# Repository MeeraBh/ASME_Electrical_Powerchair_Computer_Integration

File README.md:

# ASME Electrical Powerchair Computer Integration
This is repo contains the schematic, pcb, and gerber files from Kicad for a custom ortholinear split keyboard PCB as well as all files needed to order the pcb on JLCPCB.

This project was made for ASME - Product Development and will be shown at Engineering Open House.  

It is intended to be used for a powerchair in which the PCB contains the peripherals for the computer minus the monitor itself in which the mainboard of the computer is connected to the powerchair.  These peripherals are the keyboard itself, 2 OLED screens (Nice!Views), and 2 joysticks.  There are also a total of 3 microcontrollers (Nice!Nanos) that can connect to each other through bluetooth and communicate.  The keyboard can also be used as split design or merged together as a full keyboard due to the connections in the center.

# Keyboard
PCB

3D View Front

3D View Back

Schematic

Gerber, BOM, and CTL (.pos) files in repo that are compatible with JLCPCB printing.

Details on full project: https://erinpc.vercel.app

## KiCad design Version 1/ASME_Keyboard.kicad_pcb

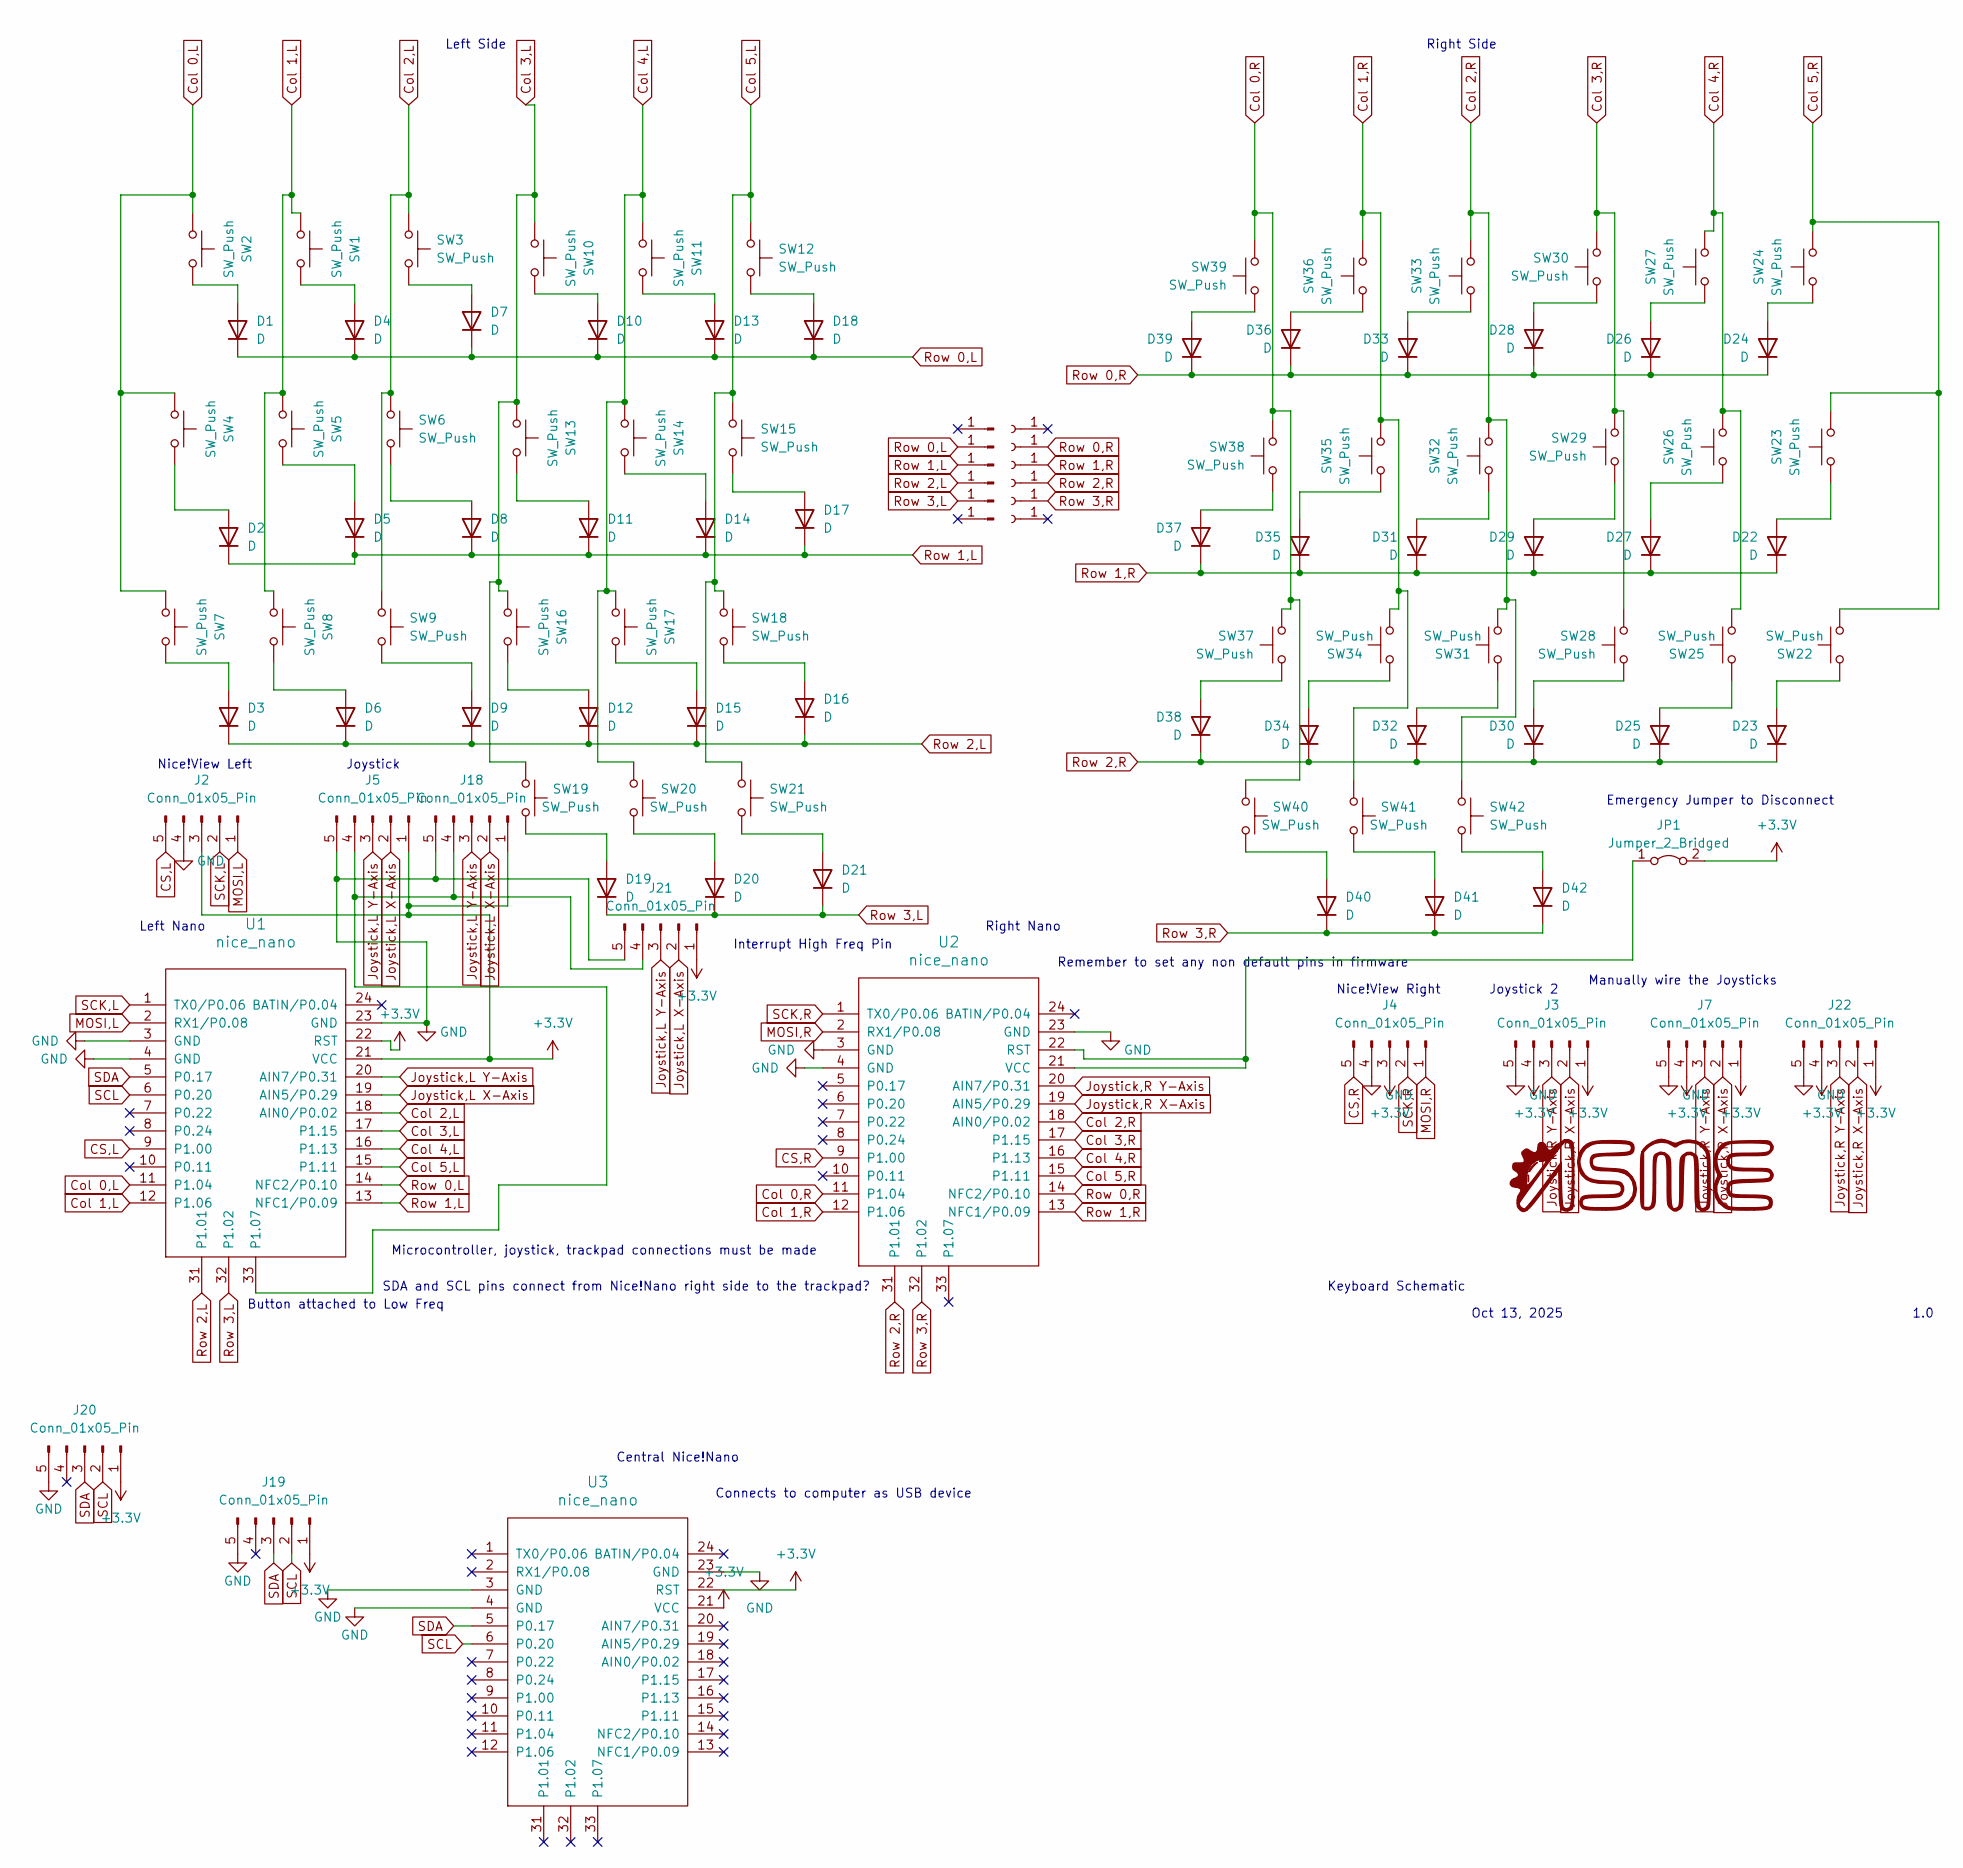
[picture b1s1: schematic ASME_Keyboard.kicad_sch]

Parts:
D1, D2, D3, D4, D5, D6, D7, D8, D9, D10, D11, D12, D13, D14, D15, D16, D17, D18, D19, D20, D21, D22, D23, D24, D25, D26, D27, D28, D29, D30, D31, D32, D33, D34, D35, D36, D37, D38, D39, D40, D41, D42: D; D_1206_3216Metric
J1, J8, J9, J10, J11, J12: Conn_01x01_Pin; MF_Connectors-POGO_PIN_70-9150
J2, J4: Conn_01x05_Pin; nice_view
J3, J5: Conn_01x05_Pin; Joycon_edited_5pin
J6, J13, J14, J15, J16, J17: Conn_01x01_Socket; MF_Connectors-POGO_PIN_70-9150
J7, J18, J19, J20, J21, J22: Conn_01x05_Pin; PinHeader_1x05_P2.54mm_Vertical
JP1: Jumper_2_Bridged; SolderJumper-2_P1.3mm_Open_Pad1.0x1.5mm
SW1, SW2, SW3, SW4, SW5, SW6, SW7, SW8, SW9, SW10, SW11, SW12, SW13, SW14, SW15, SW16, SW17, SW18, SW19, SW20, SW21, SW22, SW23, SW24, SW25, SW26, SW27, SW28, SW29, SW30, SW31, SW32, SW33, SW34, SW35, SW36, SW37, SW38, SW39, SW40, SW41, SW42: SW_Push; Kailh_socket_MX
U1, U2, U3: nice_nano

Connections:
+3.3V: J2.3, J3.1, J3.4, J4.3, J5.1, J7.1, J7.4, J18.1, J19.1, J20.1, J21.1, J22.1, J22.4, JP1.2 (B), U1.21 (VCC), U1.22 (RST), U3.21 (VCC), U3.22 (RST)
CS,L: J2.5, U1.9 (P1.00)
CS,R: J4.5, U2.9 (P1.00)
Col 0,L: SW2.1, SW4.1, SW7.1, U1.11 (P1.04)
Col 0,R: SW37.1, SW38.1, SW39.1, SW40.1, U2.11 (P1.04)
Col 1,L: SW1.1, SW5.1, SW8.1, U1.12 (P1.06)
Col 1,R: SW34.1, SW35.1, SW36.1, SW41.1, U2.12 (P1.06)
Col 2,L: SW3.1, SW6.1, SW9.1, U1.18 (AIN0/P0.02)
Col 2,R: SW31.1, SW32.1, SW33.1, SW42.1, U2.18 (AIN0/P0.02)
Col 3,L: SW10.1, SW13.1, SW16.1, SW19.1, U1.17 (P1.15)
Col 3,R: SW28.1, SW29.1, SW30.1, U2.17 (P1.15)
Col 4,L: SW11.1, SW14.1, SW17.1, SW20.1, U1.16 (P1.13)
Col 4,R: SW25.1, SW26.1, SW27.1, U2.16 (P1.13)
Col 5,L: SW12.1, SW15.1, SW18.1, SW21.1, U1.15 (P1.11)
Col 5,R: SW22.1, SW23.1, SW24.1, U2.15 (P1.11)
GND: J2.4, J3.5, J4.4, J5.5, J7.5, J18.5, J19.5, J20.5, J21.5, J22.5, U1.3 (GND), U1.4 (GND), U1.23 (GND), U2.3 (GND), U2.4 (GND), U2.23 (GND), U3.3 (GND), U3.4 (GND), U3.23 (GND)
Joystick,L X-Axis: J5.2, J18.2, J21.2, U1.19 (AIN5/P0.29)
Joystick,L Y-Axis: J5.3, J18.3, J21.3, U1.20 (AIN7/P0.31)
Joystick,R X-Axis: J3.2, J7.2, J22.2, U2.19 (AIN5/P0.29)
Joystick,R Y-Axis: J3.3, J7.3, J22.3, U2.20 (AIN7/P0.31)
MOSI,L: J2.1, U1.2 (RX1/P0.08)
MOSI,R: J4.1, U2.2 (RX1/P0.08)
unnamed: D1.2 (A), SW2.2
unnamed: D2.2 (A), SW4.2
unnamed: D3.2 (A), SW7.2
unnamed: D4.2 (A), SW1.2
unnamed: D5.2 (A), SW5.2
unnamed: D6.2 (A), SW8.2
unnamed: D7.2 (A), SW3.2
unnamed: D8.2 (A), SW6.2
unnamed: D9.2 (A), SW9.2
unnamed: D10.2 (A), SW10.2
unnamed: D11.2 (A), SW13.2
unnamed: D12.2 (A), SW16.2
unnamed: D13.2 (A), SW11.2
unnamed: D14.2 (A), SW14.2
unnamed: D15.2 (A), SW17.2
unnamed: D16.2 (A), SW18.2
unnamed: D17.2 (A), SW15.2
unnamed: D18.2 (A), SW12.2
unnamed: D19.2 (A), SW19.2
unnamed: D20.2 (A), SW20.2
unnamed: D21.2 (A), SW21.2
unnamed: D22.2 (A), SW23.2
unnamed: D23.2 (A), SW22.2
unnamed: D24.2 (A), SW24.2
unnamed: D25.2 (A), SW25.2
unnamed: D26.2 (A), SW27.2
unnamed: D27.2 (A), SW26.2
unnamed: D28.2 (A), SW30.2
unnamed: D29.2 (A), SW29.2
unnamed: D30.2 (A), SW28.2
unnamed: D31.2 (A), SW32.2
unnamed: D32.2 (A), SW31.2
unnamed: D33.2 (A), SW33.2
unnamed: D34.2 (A), SW34.2
unnamed: D35.2 (A), SW35.2
unnamed: D36.2 (A), SW36.2
unnamed: D37.2 (A), SW38.2
unnamed: D38.2 (A), SW37.2
unnamed: D39.2 (A), SW39.2
unnamed: D40.2 (A), SW40.2
unnamed: D41.2 (A), SW41.2
unnamed: D42.2 (A), SW42.2
unnamed: J5.4, J18.4, J21.4, U1.33 (P1.07)
unnamed: JP1.1 (A), U2.21 (VCC), U2.22 (RST)
Row 0,L: D1.1 (K), D4.1 (K), D7.1 (K), D10.1 (K), D13.1 (K), D18.1 (K), J1.1, U1.14 (NFC2/P0.10)
Row 0,R: D24.1 (K), D26.1 (K), D28.1 (K), D33.1 (K), D36.1 (K), D39.1 (K), J13.1, U2.14 (NFC2/P0.10)
Row 1,L: D2.1 (K), D5.1 (K), D8.1 (K), D11.1 (K), D14.1 (K), D17.1 (K), J8.1, U1.13 (NFC1/P0.09)
Row 1,R: D22.1 (K), D27.1 (K), D29.1 (K), D31.1 (K), D35.1 (K), D37.1 (K), J14.1, U2.13 (NFC1/P0.09)
Row 2,L: D3.1 (K), D6.1 (K), D9.1 (K), D12.1 (K), D15.1 (K), D16.1 (K), J9.1, U1.31 (P1.01)
Row 2,R: D23.1 (K), D25.1 (K), D30.1 (K), D32.1 (K), D34.1 (K), D38.1 (K), J15.1, U2.31 (P1.01)
Row 3,L: D19.1 (K), D20.1 (K), D21.1 (K), J10.1, U1.32 (P1.02)
Row 3,R: D40.1 (K), D41.1 (K), D42.1 (K), J16.1, U2.32 (P1.02)
SCK,L: J2.2, U1.1 (TX0/P0.06)
SCK,R: J4.2, U2.1 (TX0/P0.06)
SCL: J19.2, J20.2, U1.6 (P0.20), U3.6 (P0.20)
SDA: J19.3, J20.3, U1.5 (P0.17), U3.5 (P0.17)

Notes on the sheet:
Manually wire the Joysticks
Button attached to Low Freq
Interrupt High Freq Pin
Keyboard Schematic
Joystick 2
Oct 13, 2025
Remember to set any non default pins in firmware
Nice!View Right
SDA and SCL pins connect from Nice!Nano right side to the trackpad?
Emergency Jumper to Disconnect
Connects to computer as USB device
Microcontroller, joystick, trackpad connections must be made
Right Nano
Joystick
Left Side
Central Nice!Nano
Left Nano
1.0
Right Side
Nice!View Left

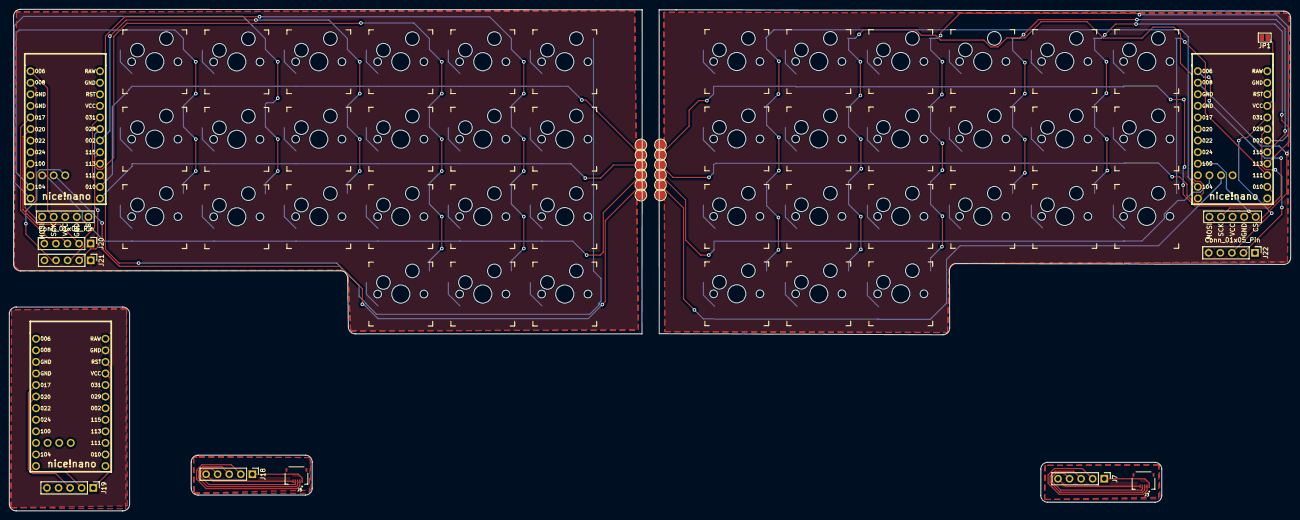
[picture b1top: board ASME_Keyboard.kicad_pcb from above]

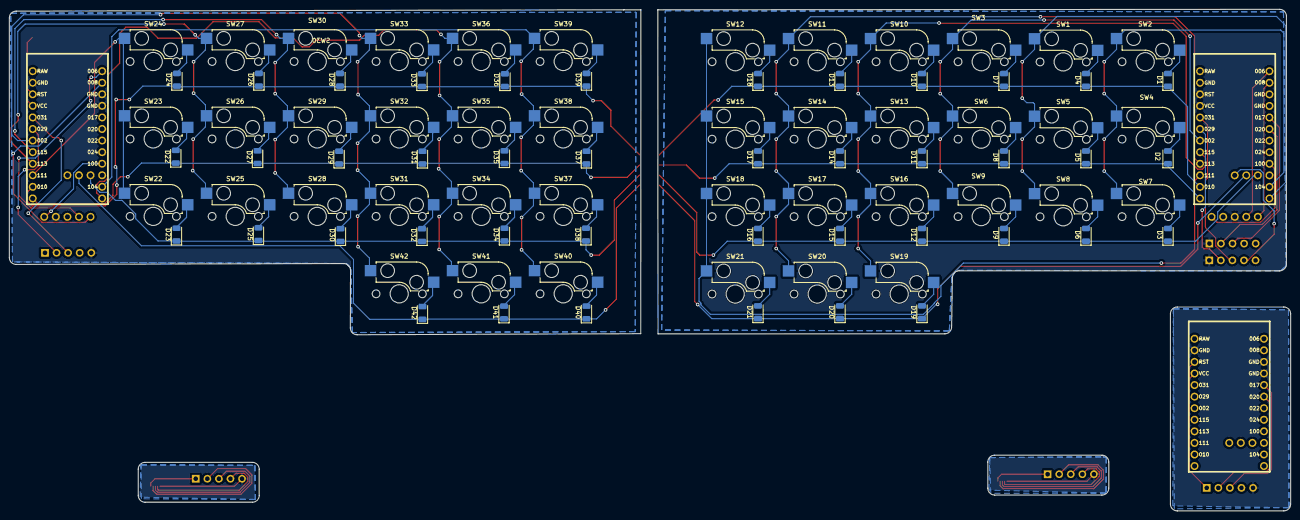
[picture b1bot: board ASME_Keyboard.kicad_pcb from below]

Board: 2 copper layers, 281.3 x 110.1 mm, 110 parts (42 on the bottom side), 78 nets.

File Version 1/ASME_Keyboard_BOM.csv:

"Id";"Designator";"Footprint";"Quantity";"Designation";"Supplier and ref";
1;"SW28,SW36,SW40,SW15,SW35,SW26,SW31,SW17,SW24,SW18,SW38,SW1,SW21,SW16,SW5,SW33,SW22,SW41,SW34,SW4,SW32,SW12,SW42,SW14,SW23,SW37,SW30,SW3,SW9,SW10,SW7,SW27,SW20,SW6,SW19,SW25,SW11,SW13,SW2,SW8,SW29,SW39";"Kailh_socket_MX";42;"SW_Push";;;
2;"J16,J17,J6,J13,J15,J14";"MF_Connectors-POGO_PIN_70-9150";6;"Conn_01x01_Socket";;;
3;"J1,J11,J10,J12,J9,J8";"MF_Connectors-POGO_PIN_70-9150";6;"Conn_01x01_Pin";;;
4;"J22,J7,J20,J21,J19,J18";"PinHeader_1x05_P2.54mm_Vertical";6;"Conn_01x05_Pin";;;
5;"U1,U2,U3";"nice_nano";3;"nice_nano";;;
6;"J4,J2";"nice_view";2;"Conn_01x05_Pin";;;
7;"J3,J5";"Joycon_edited_5pin";2;"Conn_01x05_Pin";;;
8;"JP1";"SolderJumper-2_P1.3mm_Open_Pad1.0x1.5mm";1;"Jumper_2_Bridged";;;
9;"D11,D32,D40,D28,D5,D38,D25,D12,D8,D37,D29,D9,D21,D6,D14,D7,D42,D39,D23,D19,D15,D13,D36,D17,D3,D10,D30,D22,D27,D31,D35,D4,D18,D26,D16,D20,D1,D24,D34,D41,D33,D2";"D_1206_3216Metric";42;"D";;;

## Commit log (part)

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2025-10-14 Original push of files for Keyboard
2026-03-09 All PCB files
    Need to change position file to not have negative numbers for rotations, match formatting to sent to manufacturing
2026-03-09 Pictures added
2026-03-10 Gerbers and JLCPCB Compatible Files
